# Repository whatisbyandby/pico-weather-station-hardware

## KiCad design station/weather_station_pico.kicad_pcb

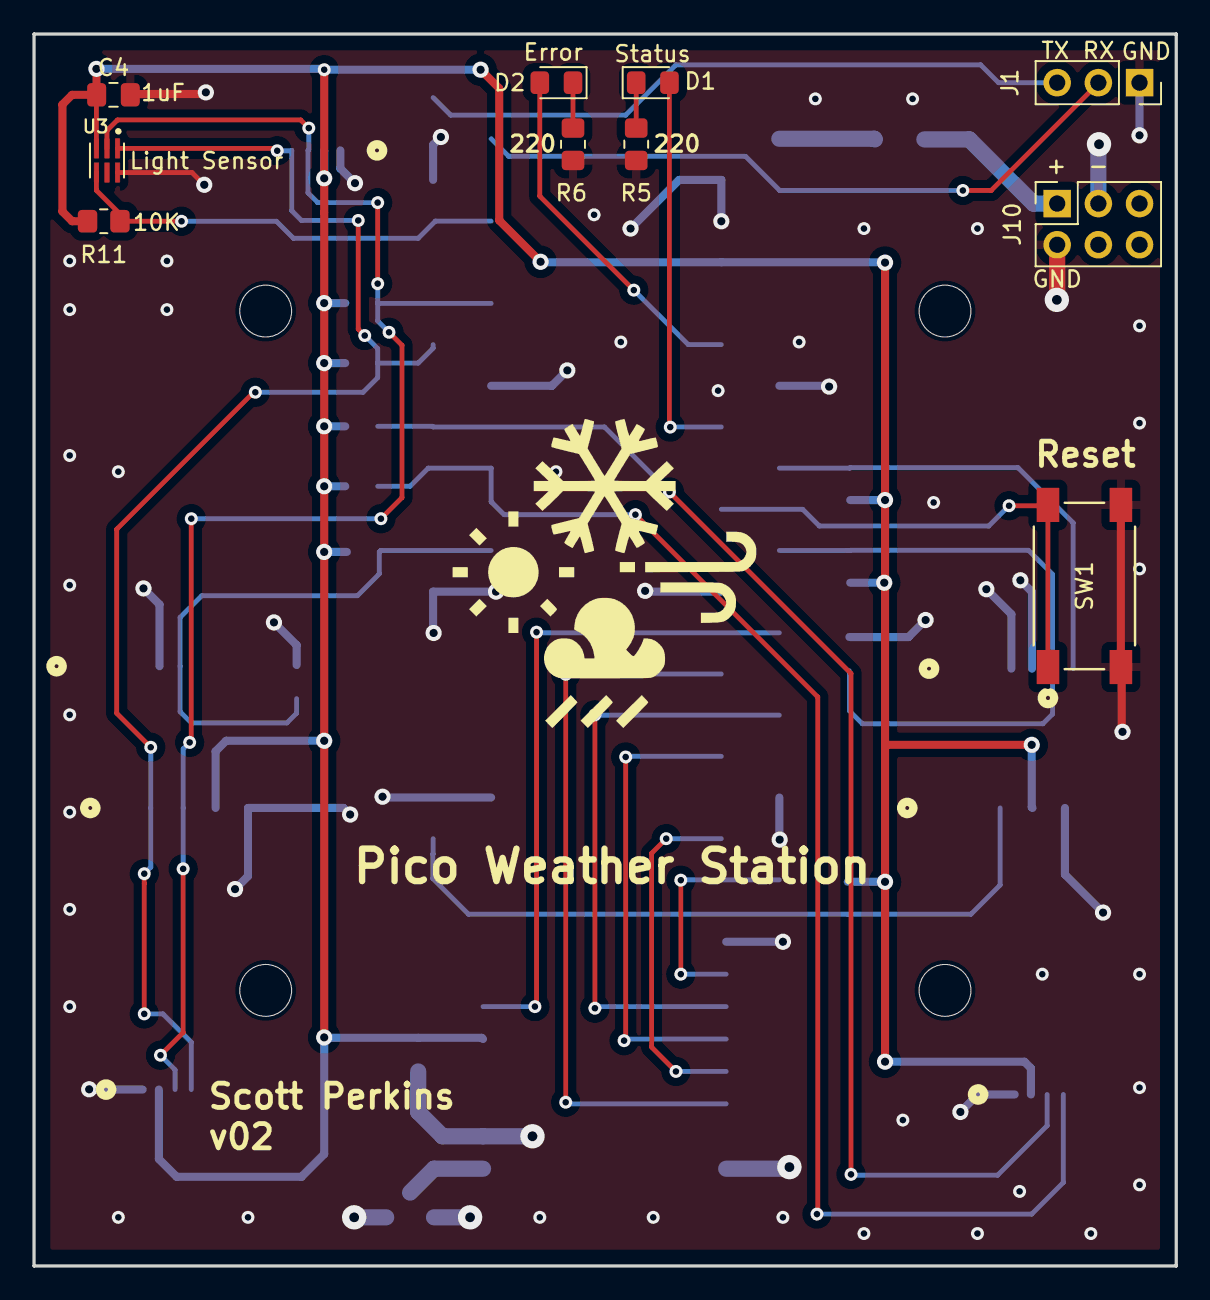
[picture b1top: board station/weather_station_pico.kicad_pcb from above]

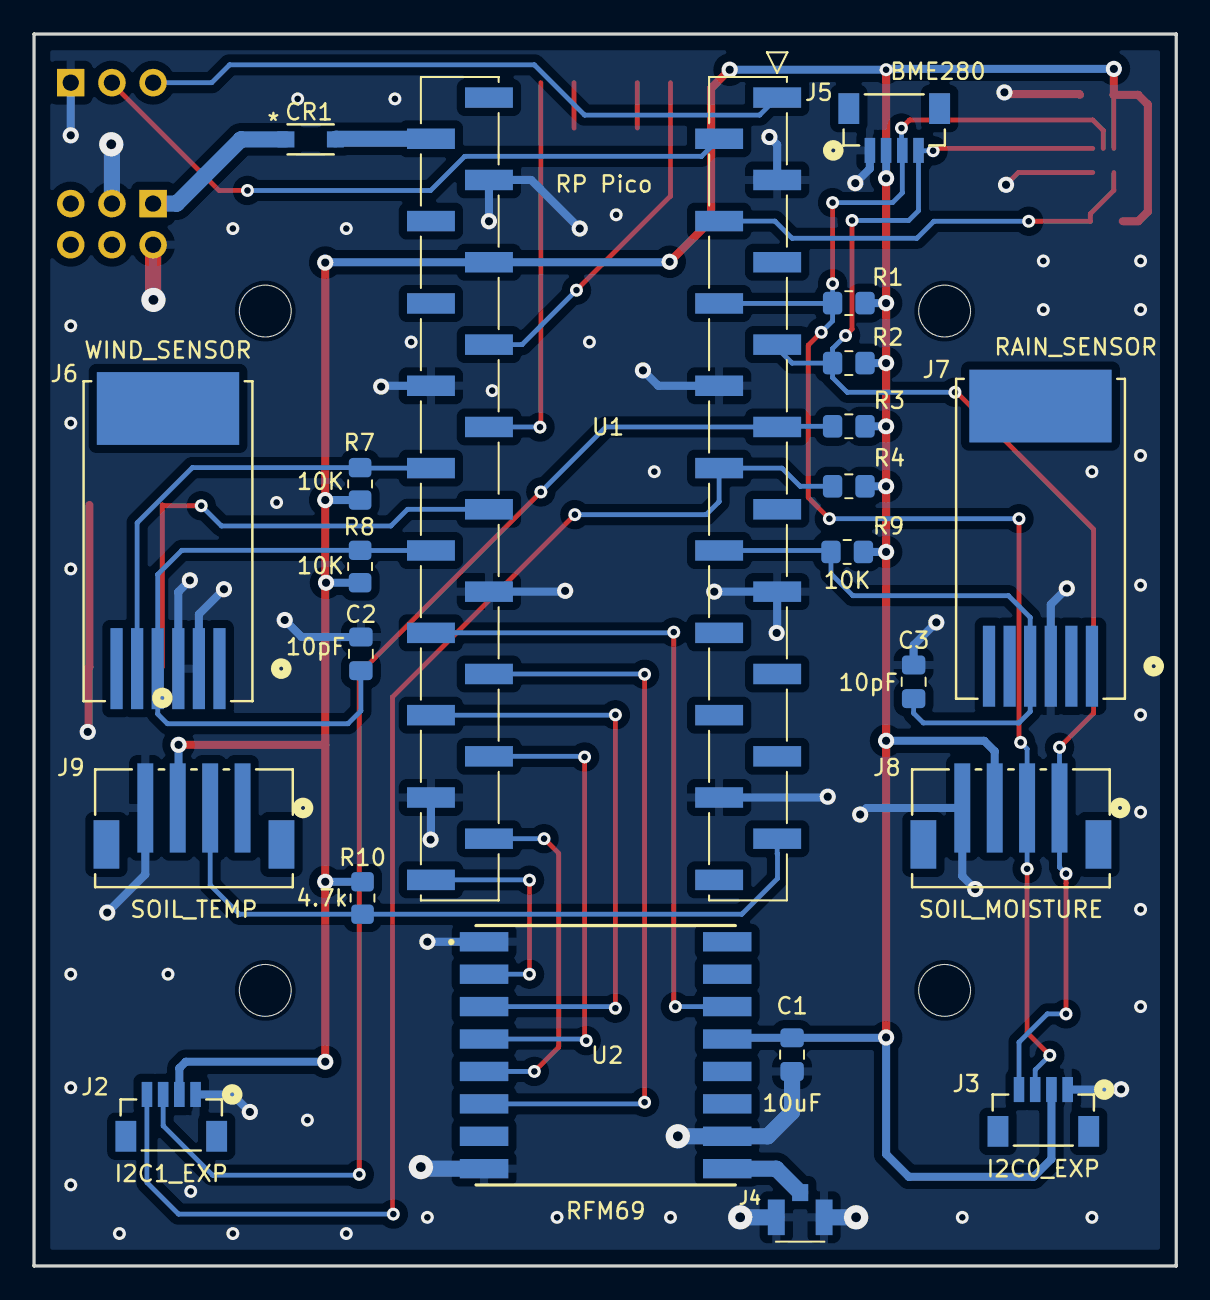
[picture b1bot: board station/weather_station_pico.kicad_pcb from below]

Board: 2 copper layers, 70.5 x 76.0 mm, 36 parts (22 on the bottom side), 27 nets.

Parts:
C1: 10uF; C_0805_2012Metric_Pad1.18x1.45mm_HandSolder
C2, C3: 10pF; C_0805_2012Metric_Pad1.18x1.45mm_HandSolder
C4: 1uF; C_0805_2012Metric_Pad1.18x1.45mm_HandSolder
CR1: SchottkyDiode
D1: GREEN; LED_0805_2012Metric_Pad1.15x1.40mm_HandSolder
D2: RED; LED_0805_2012Metric_Pad1.15x1.40mm_HandSolder
H1, H2, H3, H4: MountingHole_Pad; MountingHole_3.2mm_M3_ISO7380
J1: UART; PinSocket_1x03_P2.54mm_Vertical
J2: I2C1_EXP; StemmaQT_Vertical
J3: I2C0_EXP; StemmaQT_Vertical
J4: 73412-0110; Antenna
J5: BME280; StemmaQT_Vertical
J6: WIND_SENSOR; RJ11_SMD
J7: RAIN_SENSOR; RJ11_SMD
J8: SOIL_MOISTURE; Stemma_Vertical_Large
J9: SOIL_TEMP; Stemma_Vertical_Large
J10: Battery Charger; PinSocket_2x03_P2.54mm_Vertical
R1, R2, R3, R4: DNP; R_0805_2012Metric_Pad1.20x1.40mm_HandSolder
R5, R6: 220; R_0805_2012Metric_Pad1.20x1.40mm_HandSolder
R7, R8, R9: 10K; R_0805_2012Metric_Pad1.20x1.40mm_HandSolder
R10: 4.7k; R_0805_2012Metric_Pad1.20x1.40mm_HandSolder
R11: 10k; R_0805_2012Metric_Pad1.20x1.40mm_HandSolder
SW1: Reset Button; TactileButton
U1: Pico; Pico_SMD_Headers
U2: RFM69
U3: LIGHT_SENSOR; APDS_LIGHT_SENSOR

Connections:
+3.3V: C1.1, C4.1, J2.2, J3.2, J5.2, J8.3, J9.3, R1.1, R2.1, R3.1, R4.1, R7.1, R8.1, R9.1, R10.1, R11.1, U1.36 (3V3_OUT), U2.13 (3.3V), U3.3 (VDD)
/Battery Charger/Load+: CR1.1, J10.1
/ERROR_LED: D2.2 (A), U1.34 (GP28)
/I2C0_SCL: J3.4, J5.4, J8.1, R2.2, U1.7 (GP5), U3.1 (SCL)
/I2C0_SDA: J3.3, J5.3, J8.2, R1.2, U1.6 (GP4), U3.2 (SDA)
/I2C1_SCL: J2.4, R4.2, U1.10 (GP7)
/I2C1_SDA: J2.3, R3.2, U1.9 (GP6)
/LIGHT_INTR: R11.2, U1.4 (GP2), U3.4 (INT)
/ONE_WIRE: J9.2, R10.2, U1.19 (GP14)
/RAIN_COUNT: C3.1, J7.4, R9.2, U1.12 (GP9)
/RESET: SW1.1, SW1.2, U1.30 (~RUN)
/RFM69 Radio/RFM69_CLK: U1.24 (GP18), U2.4 (SCK)
/RFM69 Radio/RFM69_CS: U1.22 (GP17), U2.5 (NSS)
/RFM69 Radio/RFM69_INTR: U1.27 (GP21), U2.14 (DIO0)
/RFM69 Radio/RFM69_MISO: U1.21 (GP16), U2.2 (MISO)
/RFM69 Radio/RFM69_MOSI: U1.25 (GP19), U2.3 (MOSI)
/RFM69 Radio/RFM69_RESET: U1.26 (GP20), U2.6 (RESET)
/STATUS_LED: D1.2 (A), U1.32 (GP27)
/UART0_RX: J1.2, U1.2 (GP1)
/UART0_TX: J1.3, U1.1 (GP0)
/WINDDIR_OUT: J6.5, R7.2, U1.31 (GP26)
/WINDSPEED_TGR: C2.1, J6.4, R8.2, U1.29 (GP22)
GND: C1.2, C2.2, C3.2, C4.2, J1.1, J2.1, J3.1, J4.2, J4.3, J5.1, J6.2, J6.3, J7.3, J8.4, J9.4, J10.2, J10.3, R5.1, R6.1, SW1.3, SW1.4, U1.3 (GND), U1.8 (GND__1), U1.13 (GND__2), U1.18 (GND__3), U1.23 (GND__4), U1.28 (GND__5), U1.33 (AGND), U1.38 (GND__6), U2.1 (GND), U2.8 (GND__1), U2.10 (GND__2), U3.6 (GND)
unnamed: D1.1 (K), R5.2
unnamed: D2.1 (K), R6.2
unnamed: CR1.2, U1.39 (VSYS)
unnamed: J4.1, U2.9 (ANT)

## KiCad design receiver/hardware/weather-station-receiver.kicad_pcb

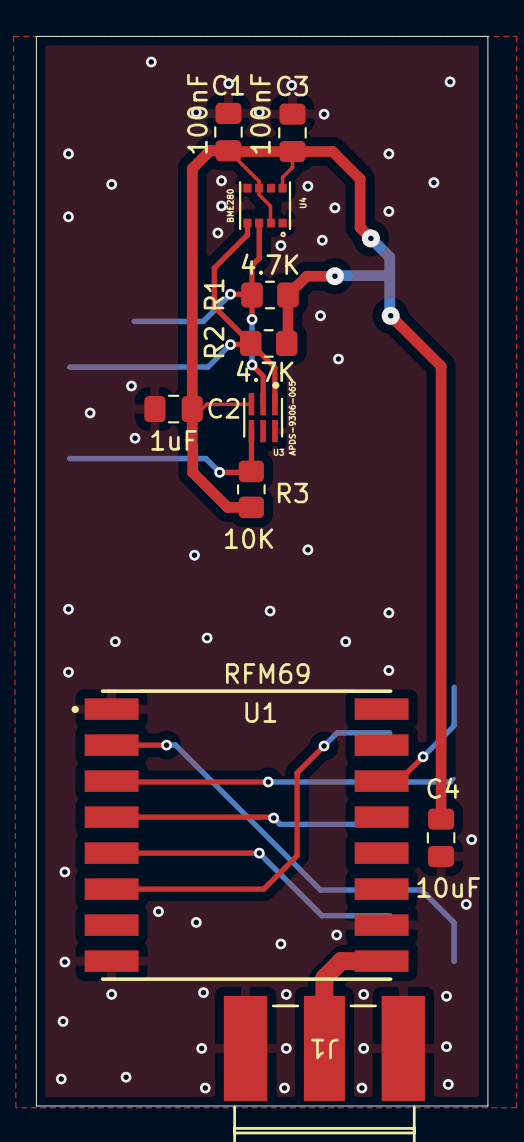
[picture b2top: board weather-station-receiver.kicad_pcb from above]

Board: 2 copper layers, 25.1 x 59.4 mm, 12 parts (1 on the bottom side), 12 nets.

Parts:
C1, C3: 100nF; C_0805_2012Metric_Pad1.18x1.45mm_HandSolder
C2: 1uF; C_0805_2012Metric_Pad1.18x1.45mm_HandSolder
C4: 10uF; C_0805_2012Metric_Pad1.18x1.45mm_HandSolder
J1: BoardAntennaConnector; PCB_Antenna
R1, R2: 4.7K; R_0805_2012Metric_Pad1.20x1.40mm_HandSolder
R3: 10K; R_0805_2012Metric_Pad1.20x1.40mm_HandSolder
U1: RFM69
U2: PicoW; Pico_SMD_Headers
U3: APDS-9306-065; LightSensor
U4: BME280

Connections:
+3.3V: C1.1, C2.1, C3.1, C4.1, R1.1, R2.1, R3.1, U1.13 (3.3V), U2.36 (3V3_OUT), U3.3 (VDD), U4.2 (CSB), U4.6 (VDDIO), U4.8 (VDD)
/APDS_INTR: R3.2, U2.9 (GP6), U3.4 (INT)
/I2C0_SCL: R2.2, U2.7 (GP5), U3.1 (SCL), U4.4 (SCK)
/I2C0_SDA: R1.2, U2.6 (GP4), U3.2 (SDA), U4.3 (SDI)
/RFM69_CS: U1.5 (NSS), U2.22 (GP17)
/RFM69_INTR: U1.14 (DIO0), U2.27 (GP21)
/RFM69_RESET: U1.6 (RESET), U2.26 (GP20)
/SPI0_CLK: U1.4 (SCK), U2.24 (GP18)
/SPI0_MISO: U1.2 (MISO), U2.21 (GP16)
/SPI0_MOSI: U1.3 (MOSI), U2.25 (GP19)
GND: C1.2, C2.2, C3.2, C4.2, J1.2, J1.3, U1.1 (GND), U1.8 (GND__1), U1.10 (GND__2), U2.3 (GND), U2.8 (GND__1), U2.13 (GND__2), U2.18 (GND__3), U2.23 (GND__4), U2.28 (GND__5), U2.33 (AGND), U2.38 (GND__6), U3.6 (GND), U4.1 (GND), U4.5 (SDO), U4.7 (GND__1)
unnamed: J1.1, U1.9 (ANT)

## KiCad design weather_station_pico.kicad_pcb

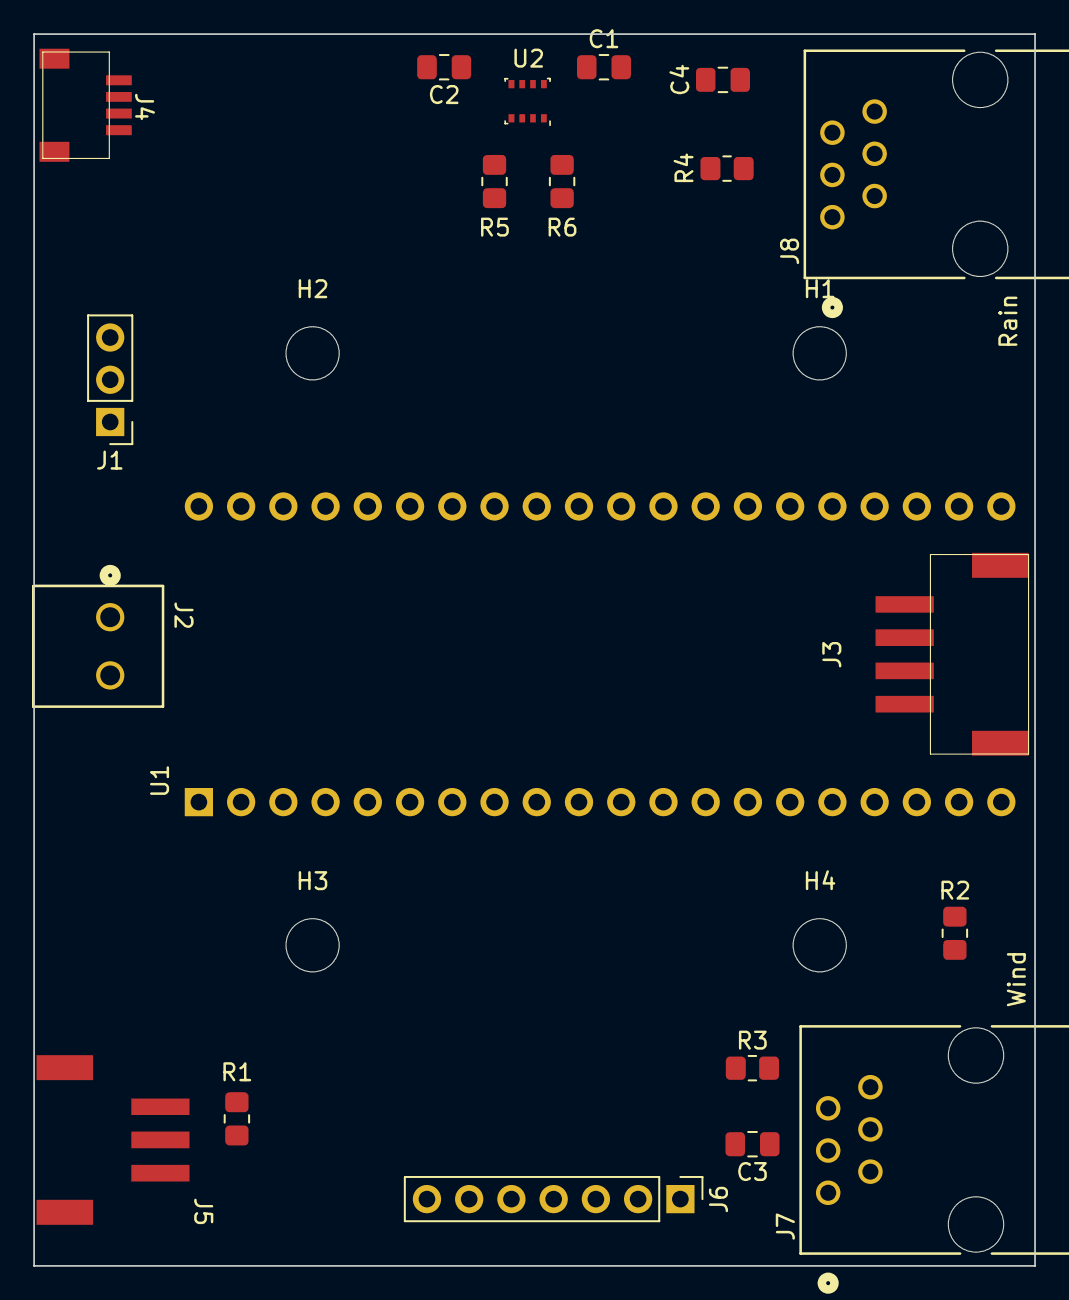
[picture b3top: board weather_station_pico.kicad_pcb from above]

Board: 2 copper layers, 60.2 x 74.1 mm, 24 parts (0 on the bottom side), 11 nets.

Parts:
C1, C2: 100nF; C_0805_2012Metric_Pad1.18x1.45mm_HandSolder
C3, C4: 10pF; C_0805_2012Metric_Pad1.18x1.45mm_HandSolder
H1, H2, H3, H4: MountingHole_Pad; MountingHole_3.2mm_M3_ISO7380
J1: UART_DEBUG; PinHeader_1x03_P2.54mm_Vertical
J2: 1984617; CONN_1984617_PXC
J3: STEMMA; STEMMA_LARGE
J4: STEMMA_QT; STEMMA_SMALL
J5: DS18B20; STEMMA_LARGE_3pin
J6: 1X7_HEADER; PinHeader_1x07_P2.54mm_Vertical
J7, J8: RJ11; CONN6_5555165-1_TEC
R1: R; R_0805_2012Metric_Pad1.20x1.40mm_HandSolder
R2, R3, R4: 10K; R_0805_2012Metric_Pad1.20x1.40mm_HandSolder
R5, R6: 4.7K; R_0805_2012Metric_Pad1.20x1.40mm_HandSolder
U1: PICO_W; PinHeader_2x20_P2.54mm_Vertical
U2: BME280; Bosch_LGA-8_2.5x2.5mm_P0.65mm_ClockwisePinNumbering

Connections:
+5V: J2.2, U1.39 (VSYS)
/ONE_WIRE: J5.1, R1.1, U1.20 (GP15)
/RAIN_COUNT: C4.1, J8.4, R4.2, U1.6 (GP4)
/SCL: J3.4, J4.4, R5.2, U1.17 (GP13), U2.4 (SCK)
/SDA: J3.3, J4.3, R6.2, U1.16 (GP12), U2.3 (SDI)
/UART_RX: J1.2, U1.2 (GP1)
/UART_TX: J1.3, U1.1 (GP0)
/WINDDIR_OUT: J7.5, R2.2, U1.31 (GP26)
/WINDSPEED_TGR: C3.1, J7.4, R3.2, U1.29 (GP22)
GND: C1.2, C2.2, C3.2, C4.2, J1.1, J2.1, J3.1, J4.1, J5.3, J6.7, J7.2, J7.3, J8.3, U1.3 (GND), U1.8 (GND__1), U1.13 (GND__2), U1.18 (GND__3), U1.23 (GND__4), U1.28 (GND__5), U1.33 (AGND), U1.38 (GND__6), U2.1 (GND), U2.5 (SDO), U2.7 (GND)
VCC: C1.1, C2.1, J3.2, J4.2, J5.2, J6.6, R1.2, R2.1, R3.1, R4.1, R5.1, R6.1, U1.36 (3V3_OUT), U2.2 (CSB), U2.6 (VDDIO), U2.8 (VDD)

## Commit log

2024-03-24 Added gitignore
2024-03-24 Added Pico Component
2024-03-25 Added footprints for antenna connector
2024-03-28 Reorganized the repo
2024-03-29 Finished Layout
2024-04-01 Updated the weather stations components
2024-04-02 Reworked layout
2024-04-03 Switched to a round board
2024-04-04 Finished Circular Layout
2024-04-04 Finished Square layout
2024-04-04 Updated the I2C schematic for the soil moisture sensor
2024-04-05 Added a reset button, status LEDs and broke out UART pins
2024-04-05 V01 of the board complete
2024-04-06 Final Touches
2024-04-22 Finished with V1 Board
2024-04-22 Fixed a defect where to wrong pins of the reset button were shorted together, causing the pico board to be in a constant reset state
2025-07-06 Creating branch for V2
2025-11-01 Resolved merge conflicts
